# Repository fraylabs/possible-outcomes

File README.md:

# Fray Labs Outcomes

Public, reusable AI Outcomes and the recipes behind them, published by Fray Labs for [Possible](https://possible.sh).

Each folder contains:

- `outcome.md` — what was made and the original request;
- `prompt.md` — the recorded reusable execution prompt; and
- `outcome.json` — provenance, models, Products, Skills, requirements, file metadata, and an optional recipe.

A recipe collects the recorded agent, pinned skills, references, tools and ordered steps that help another agent reproduce or adapt the result. Unknown details are omitted. Fray-authored backfills explicitly label steps reconstructed from published prompts and artifacts; they are not transcripts of historical agent turns. Existing model provenance, prompts, result limitations and creator credits remain intact. Curated third-party demos retain their disclosed prompts without an invented workflow.

The root [`outcomes.json`](./outcomes.json) is the machine-readable publisher index. Possible reads this repository directly; the canonical source remains here.

## Use with Possible

Use CLI 0.5.0 or newer for manifests containing the optional `recipe` field. The older primary Product/Skill parsing issue in CLI 0.3.0 was fixed in 0.3.1; recipe support began in 0.4.0; explicit reconstructed-origin labels require 0.5.0.

```shell
npx https://github.com/fraylabs/possible/releases/download/v0.5.0/fraylabs-possible-0.5.0.tgz add fraylabs/possible-outcomes
npx https://github.com/fraylabs/possible/releases/download/v0.5.0/fraylabs-possible-0.5.0.tgz use fraylabs/possible-outcomes@digital-photo-frame
```

The `use` command provides the reusable instructions for an agent. Review the recipe, original prompt and stated limits before running it; access to referenced tools and services is still required.

## Opus 5.5 demos

[See ten creator demos and copy their prompts](OPUS-DEMOS.md): neon cities, mini golf, a cursor-following pet, a rocket launch, an interactive robot hand, fluid simulation, a Rube Goldberg machine, a sunset pirate ship, motion design and an explorable pagoda. Each links the original creator and records creator-reported model provenance.

## License

Fray-authored code and text are available under the MIT License. Curated creator prompts and demo media retain their original ownership and are excluded from that grant; see linked sources and each media/NOTICE.md. Referenced third-party Products and Skills retain their respective ownership and licenses.

CLI 0.5.0 is currently distributed through the verified GitHub release package used above. The npm registry remains on 0.3.1; use the release package for these optional recipes.

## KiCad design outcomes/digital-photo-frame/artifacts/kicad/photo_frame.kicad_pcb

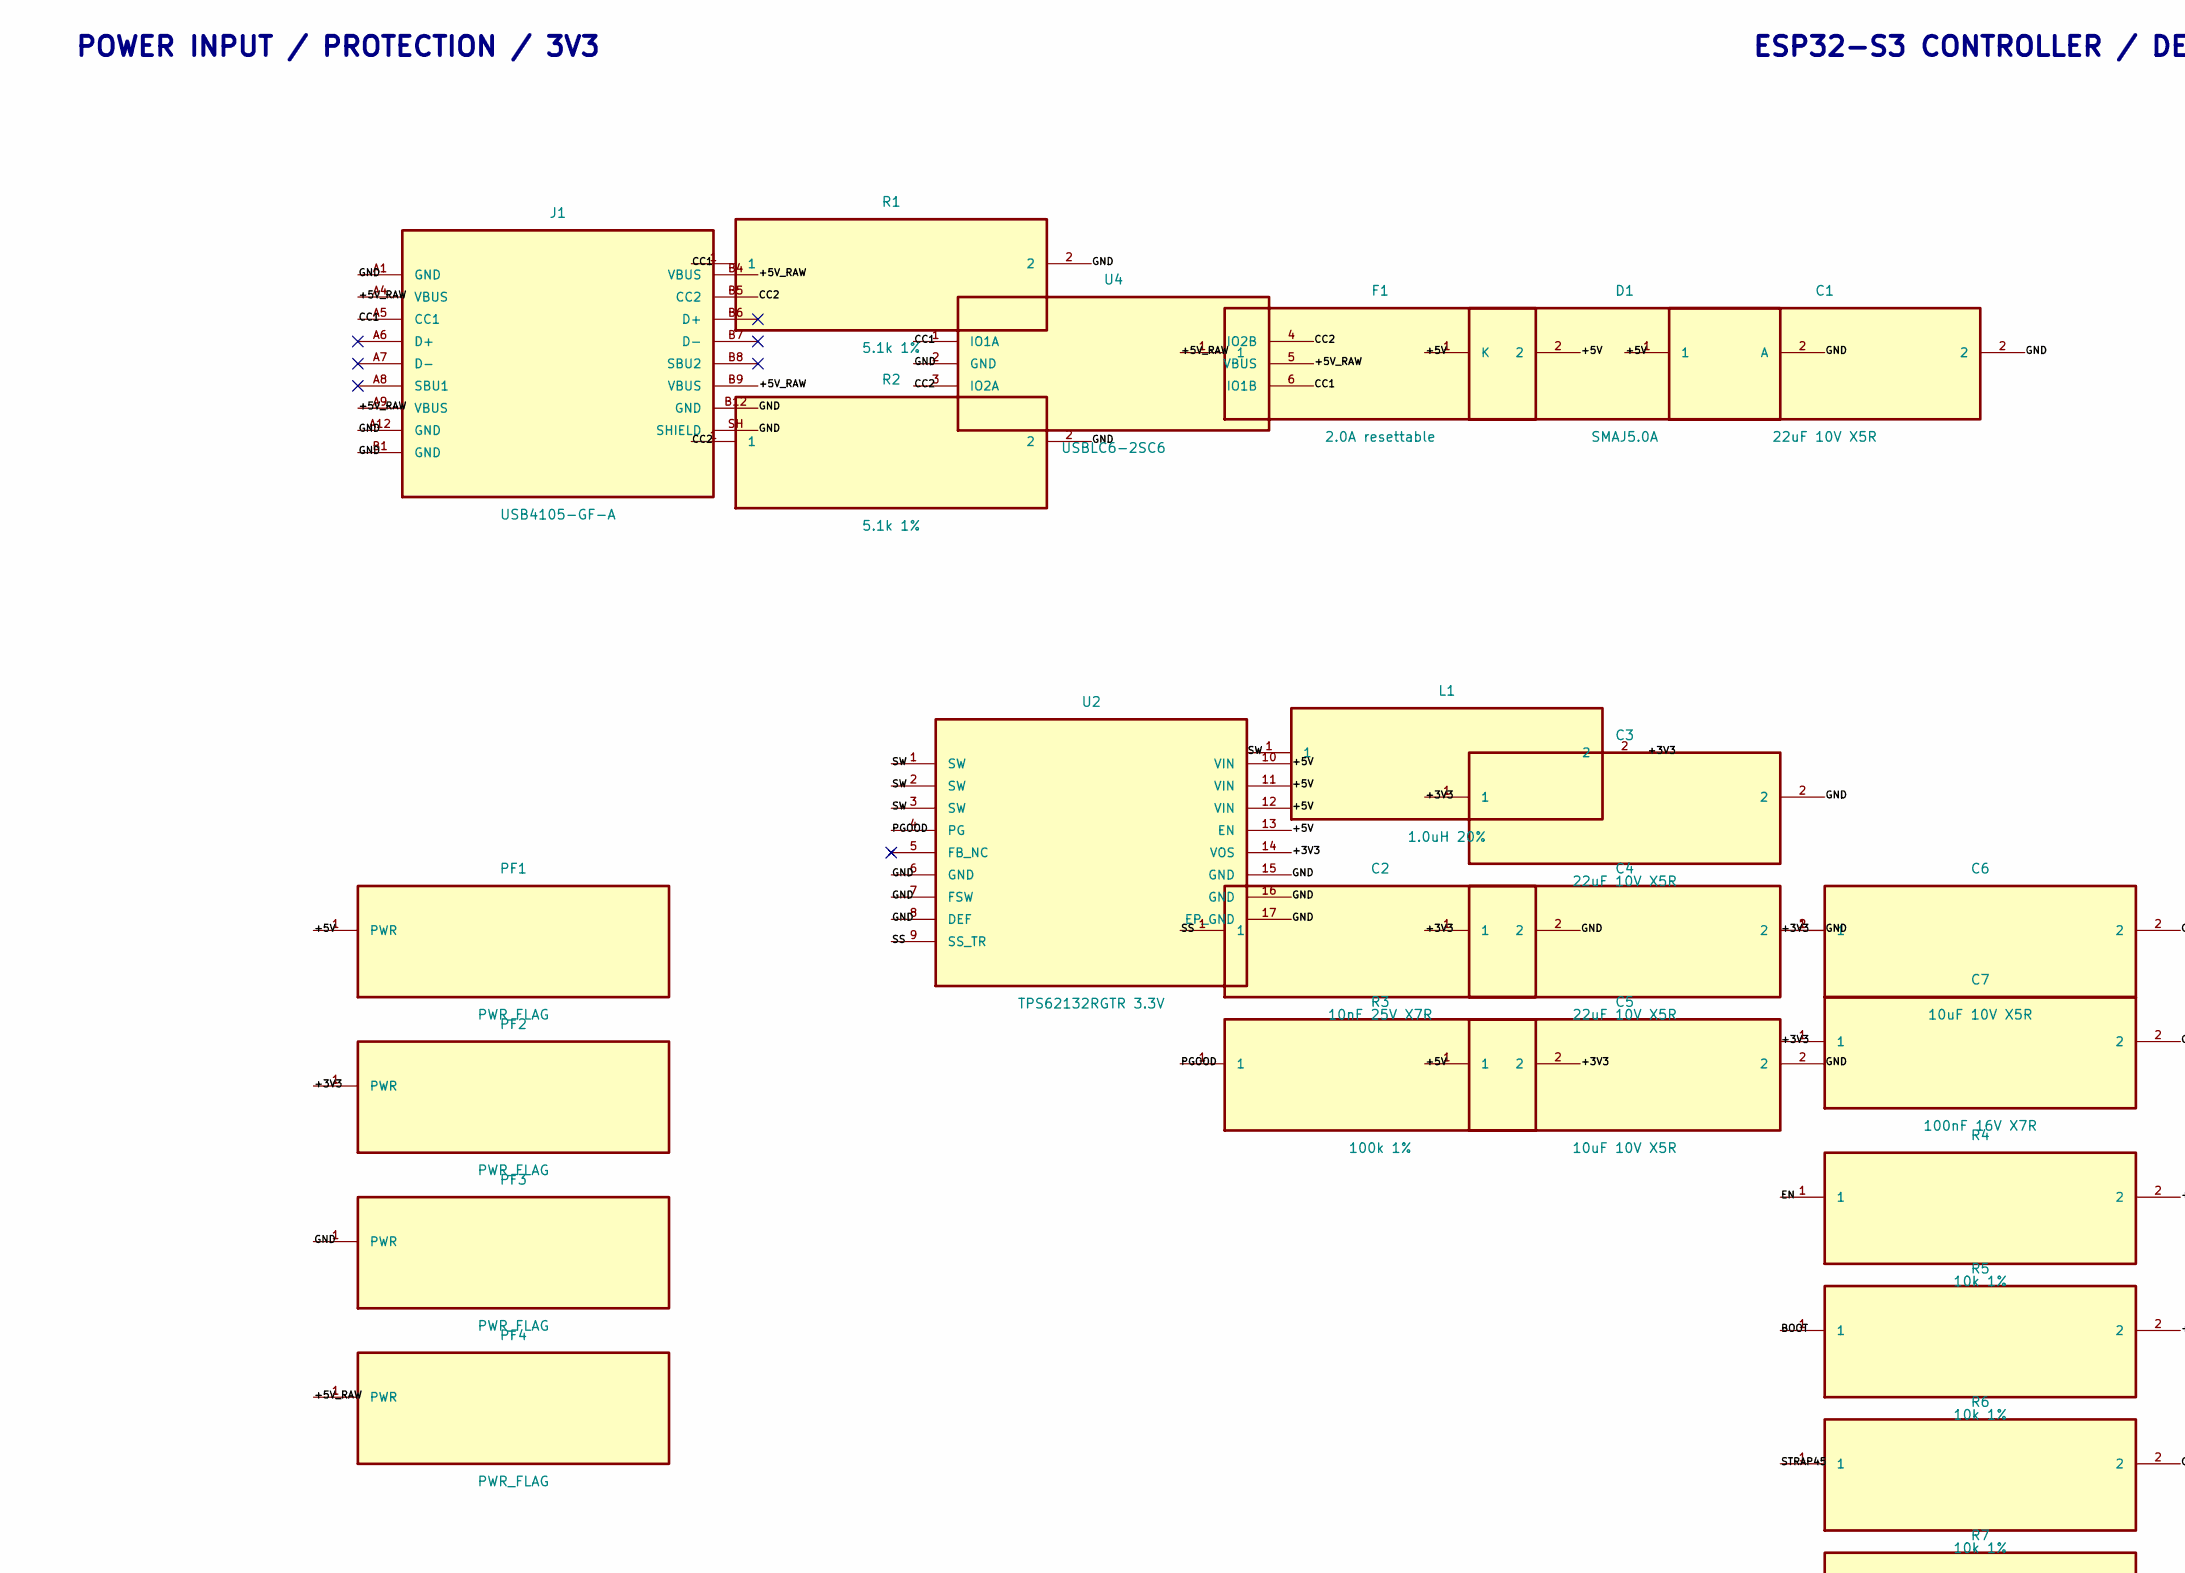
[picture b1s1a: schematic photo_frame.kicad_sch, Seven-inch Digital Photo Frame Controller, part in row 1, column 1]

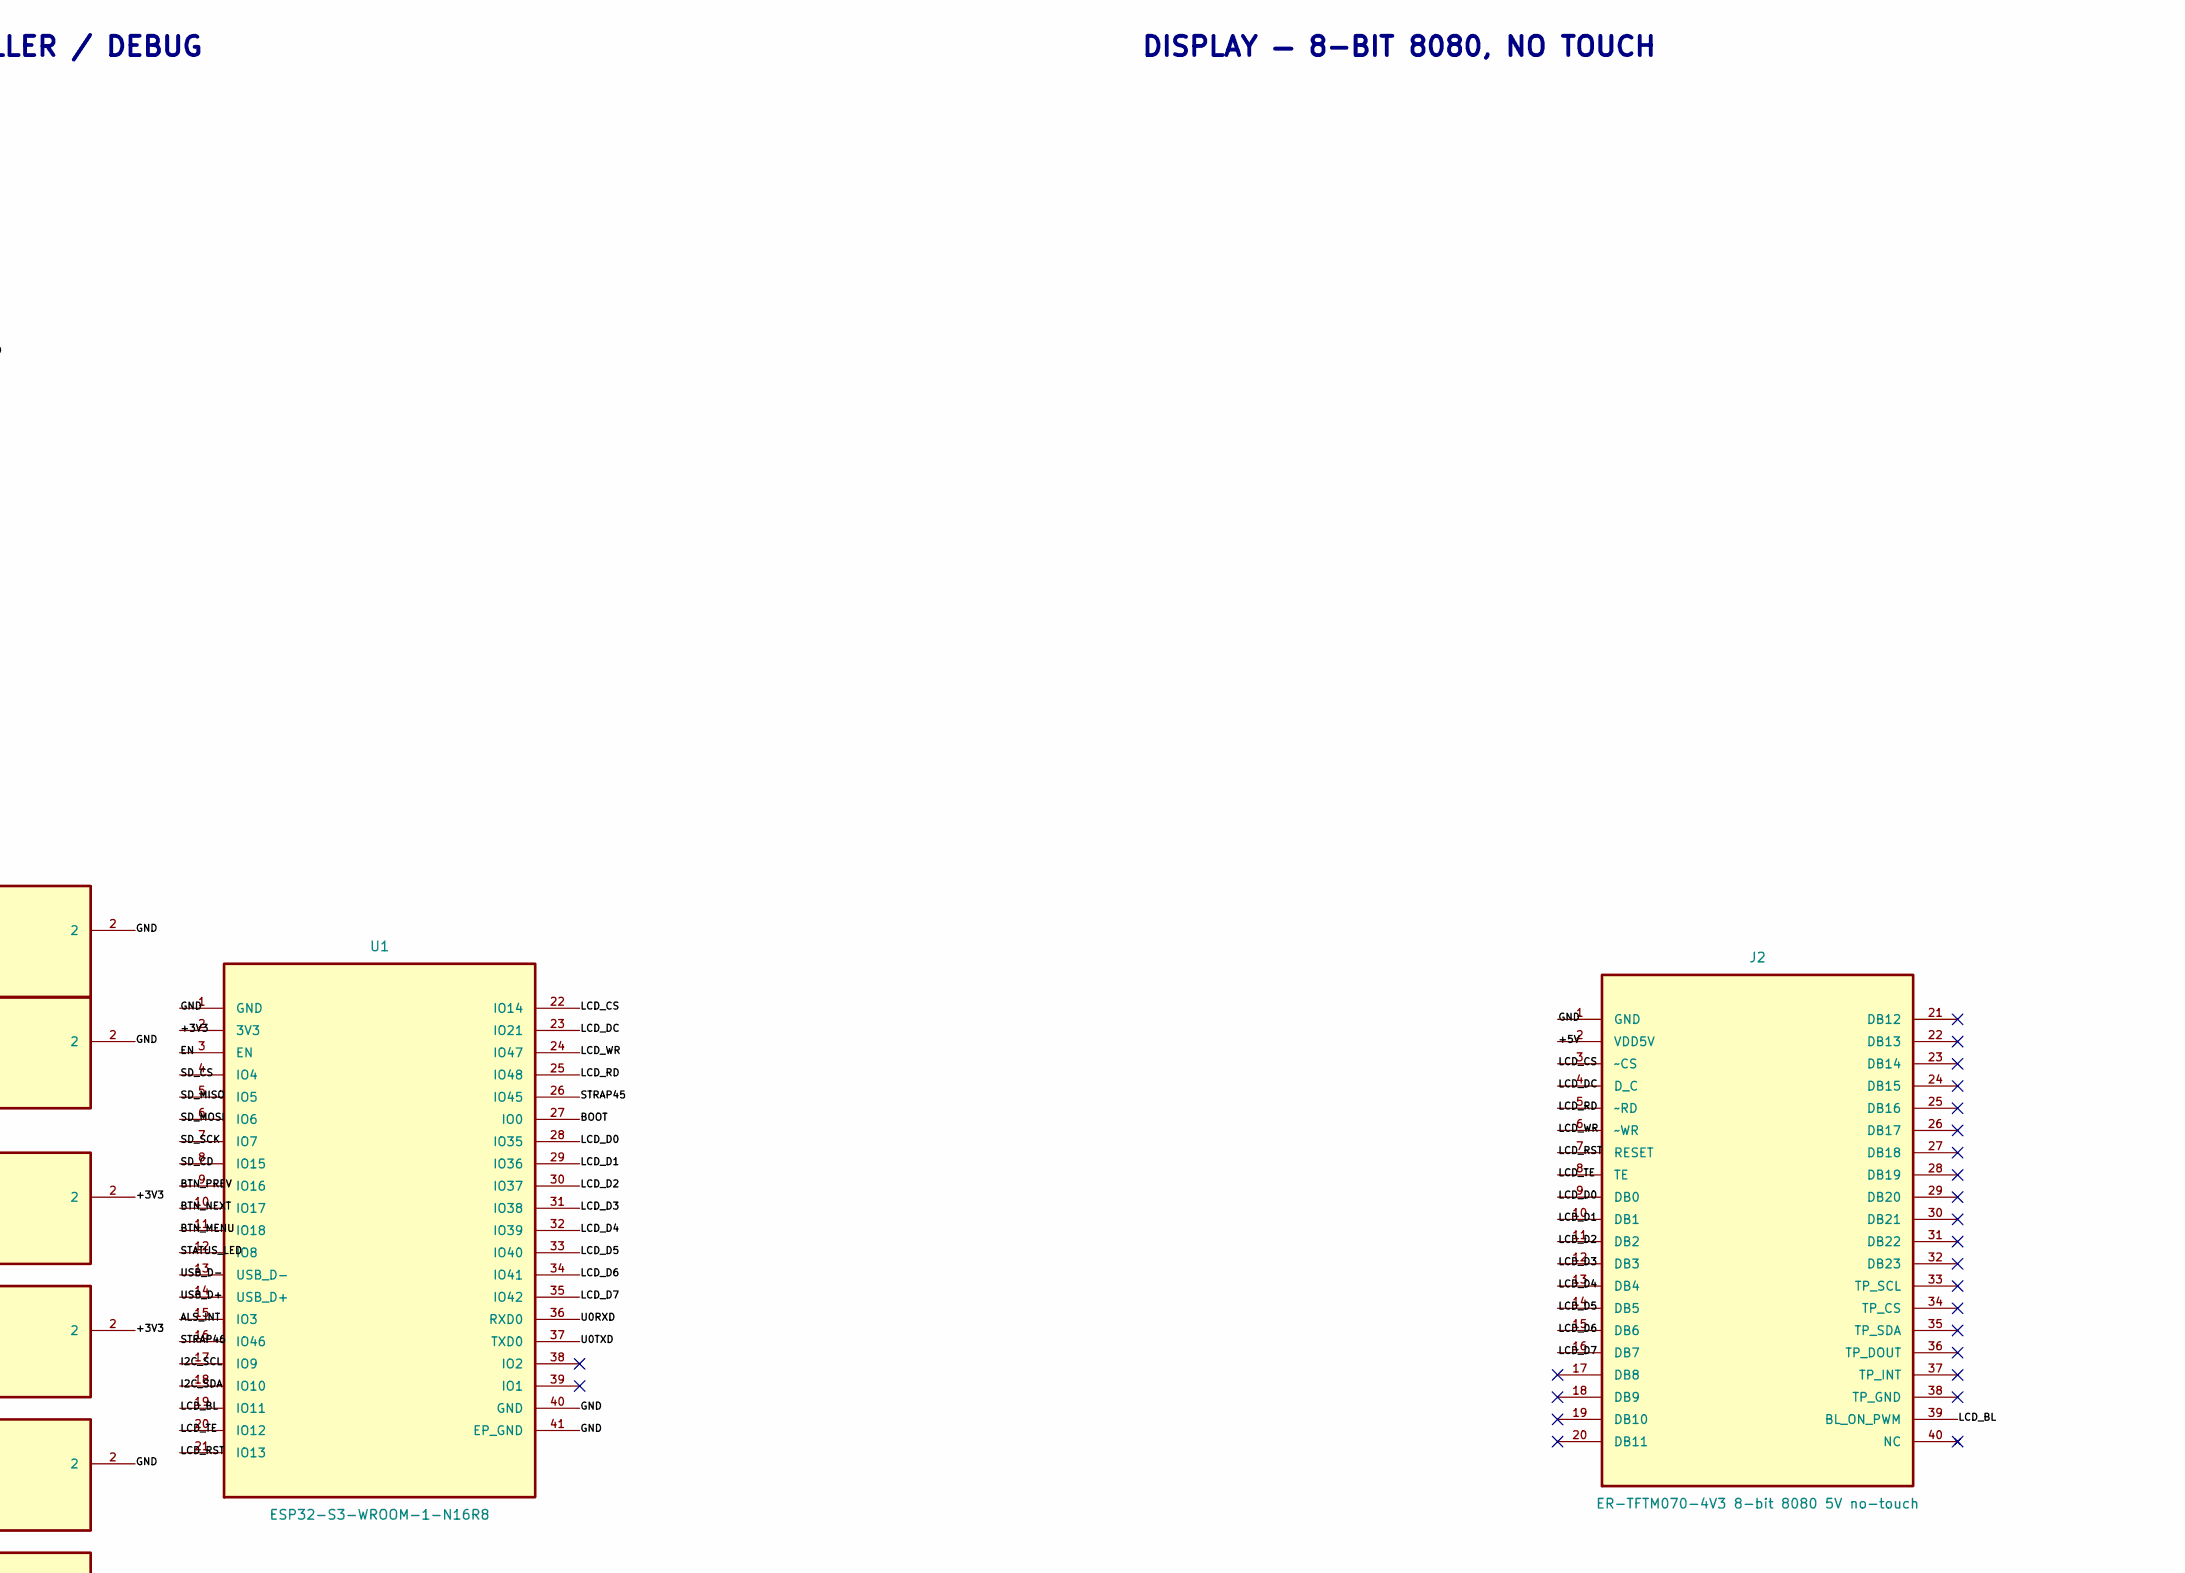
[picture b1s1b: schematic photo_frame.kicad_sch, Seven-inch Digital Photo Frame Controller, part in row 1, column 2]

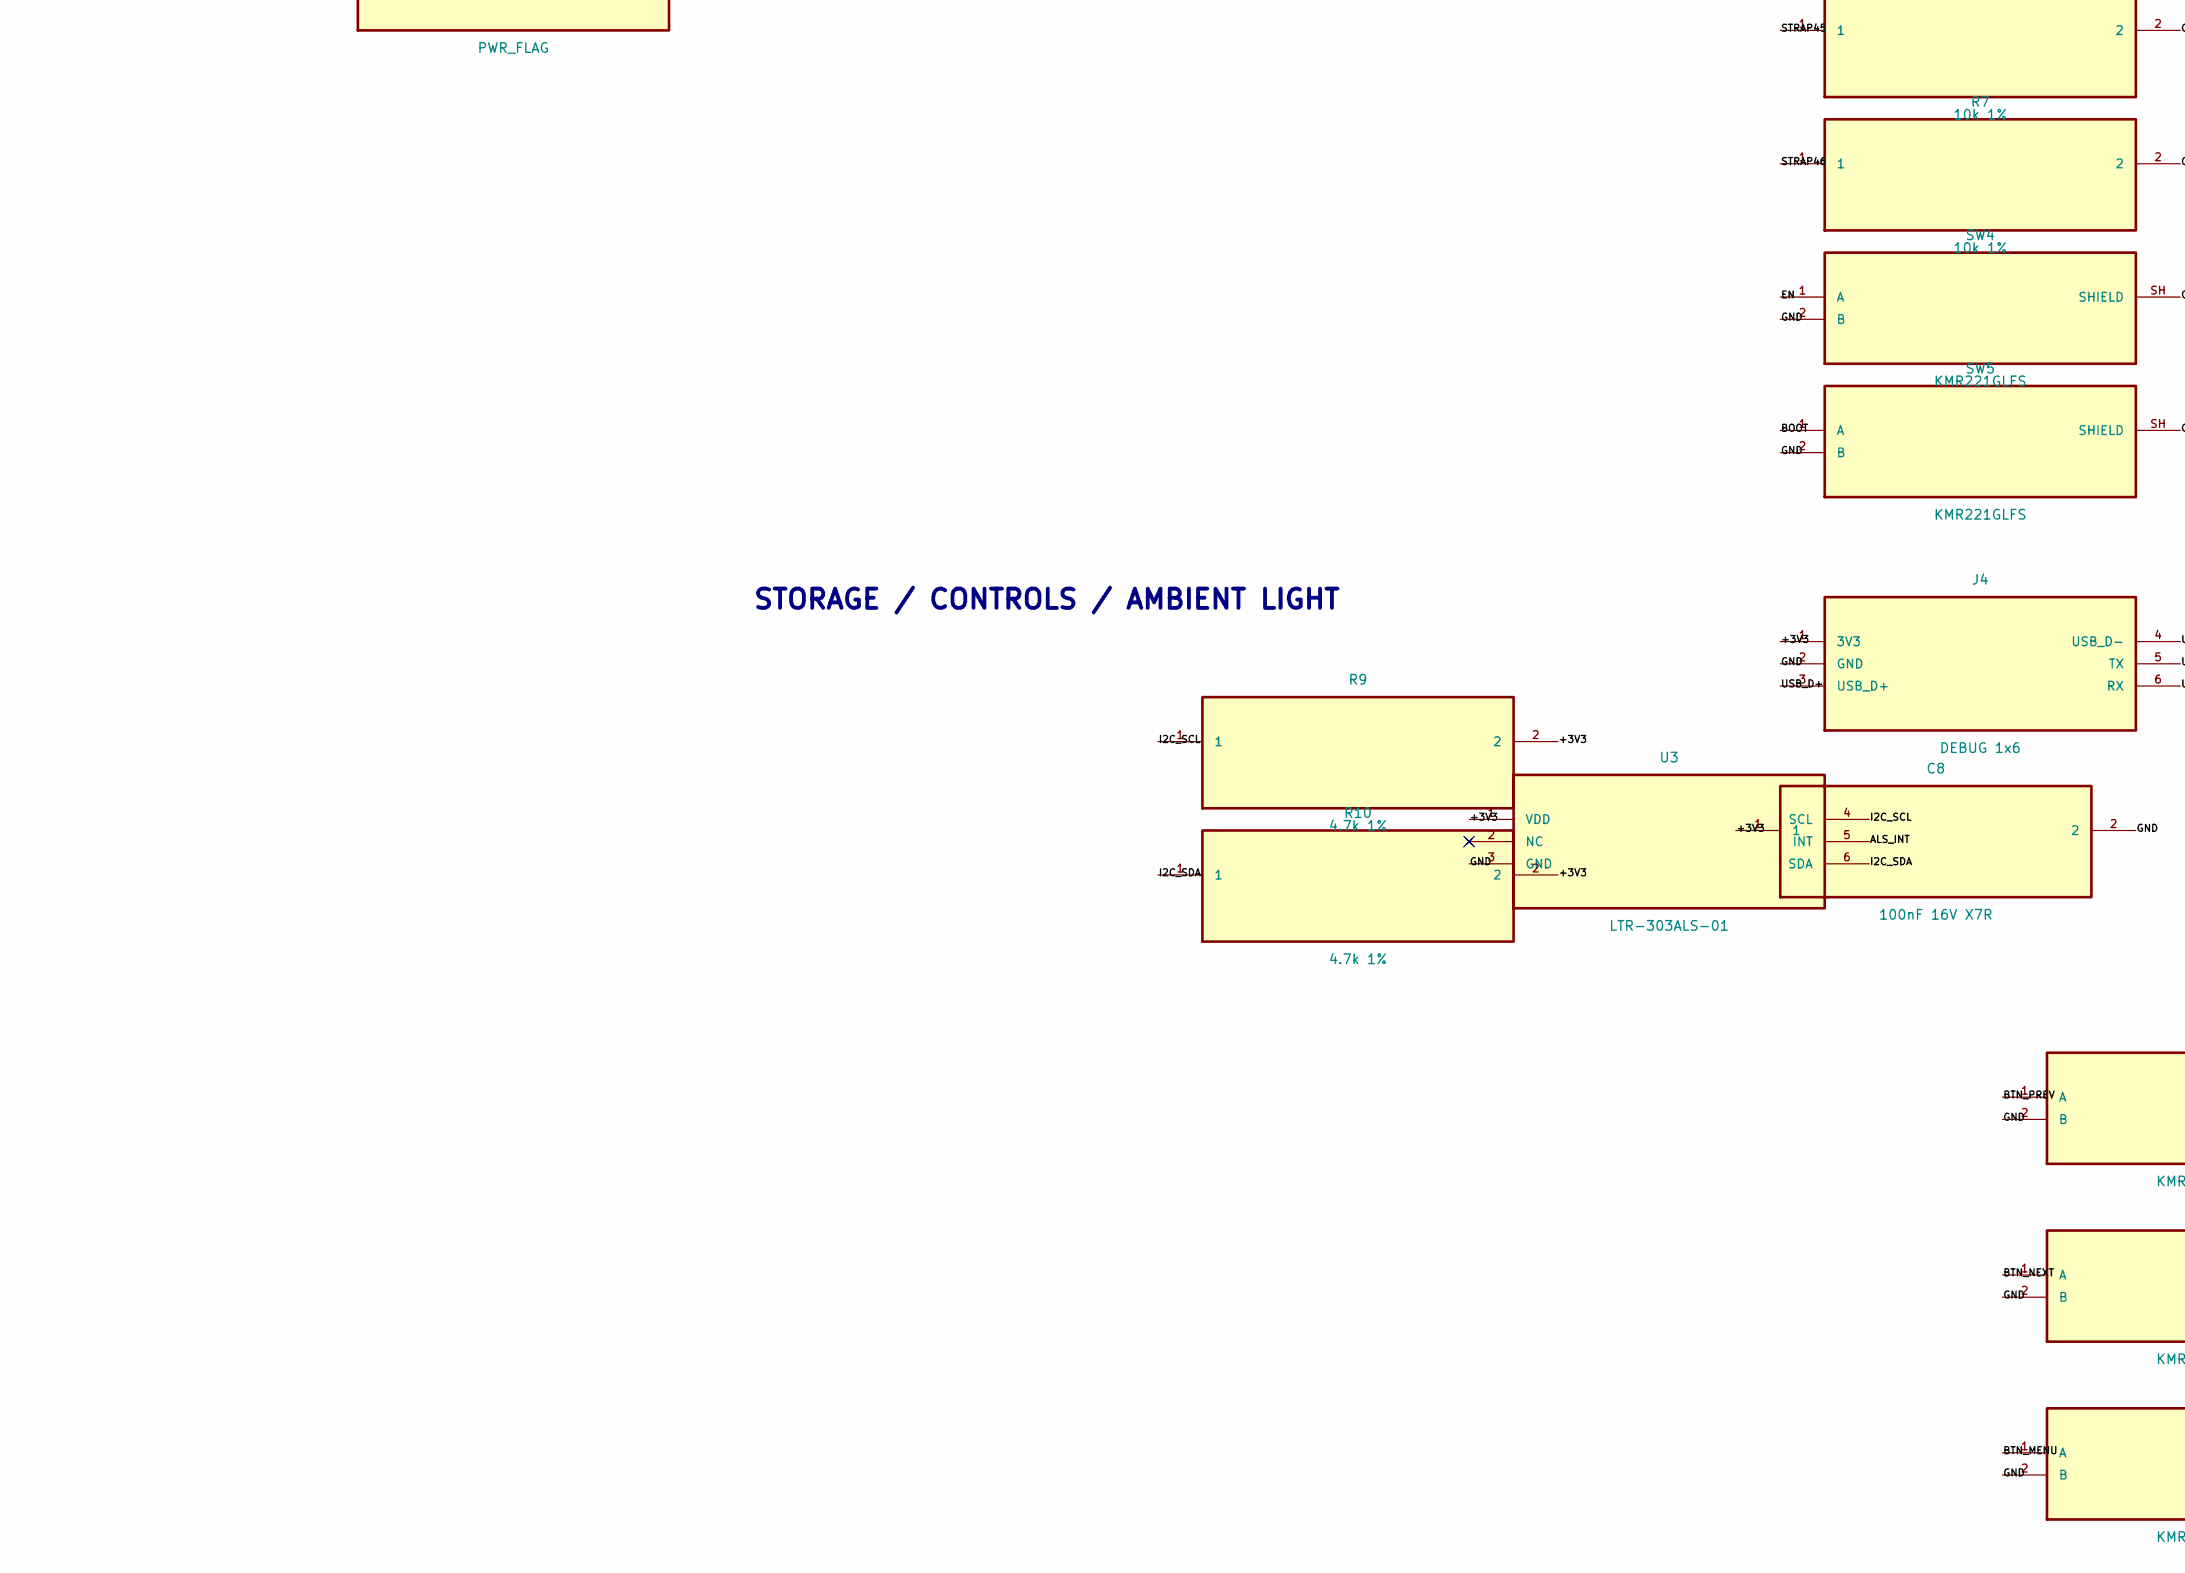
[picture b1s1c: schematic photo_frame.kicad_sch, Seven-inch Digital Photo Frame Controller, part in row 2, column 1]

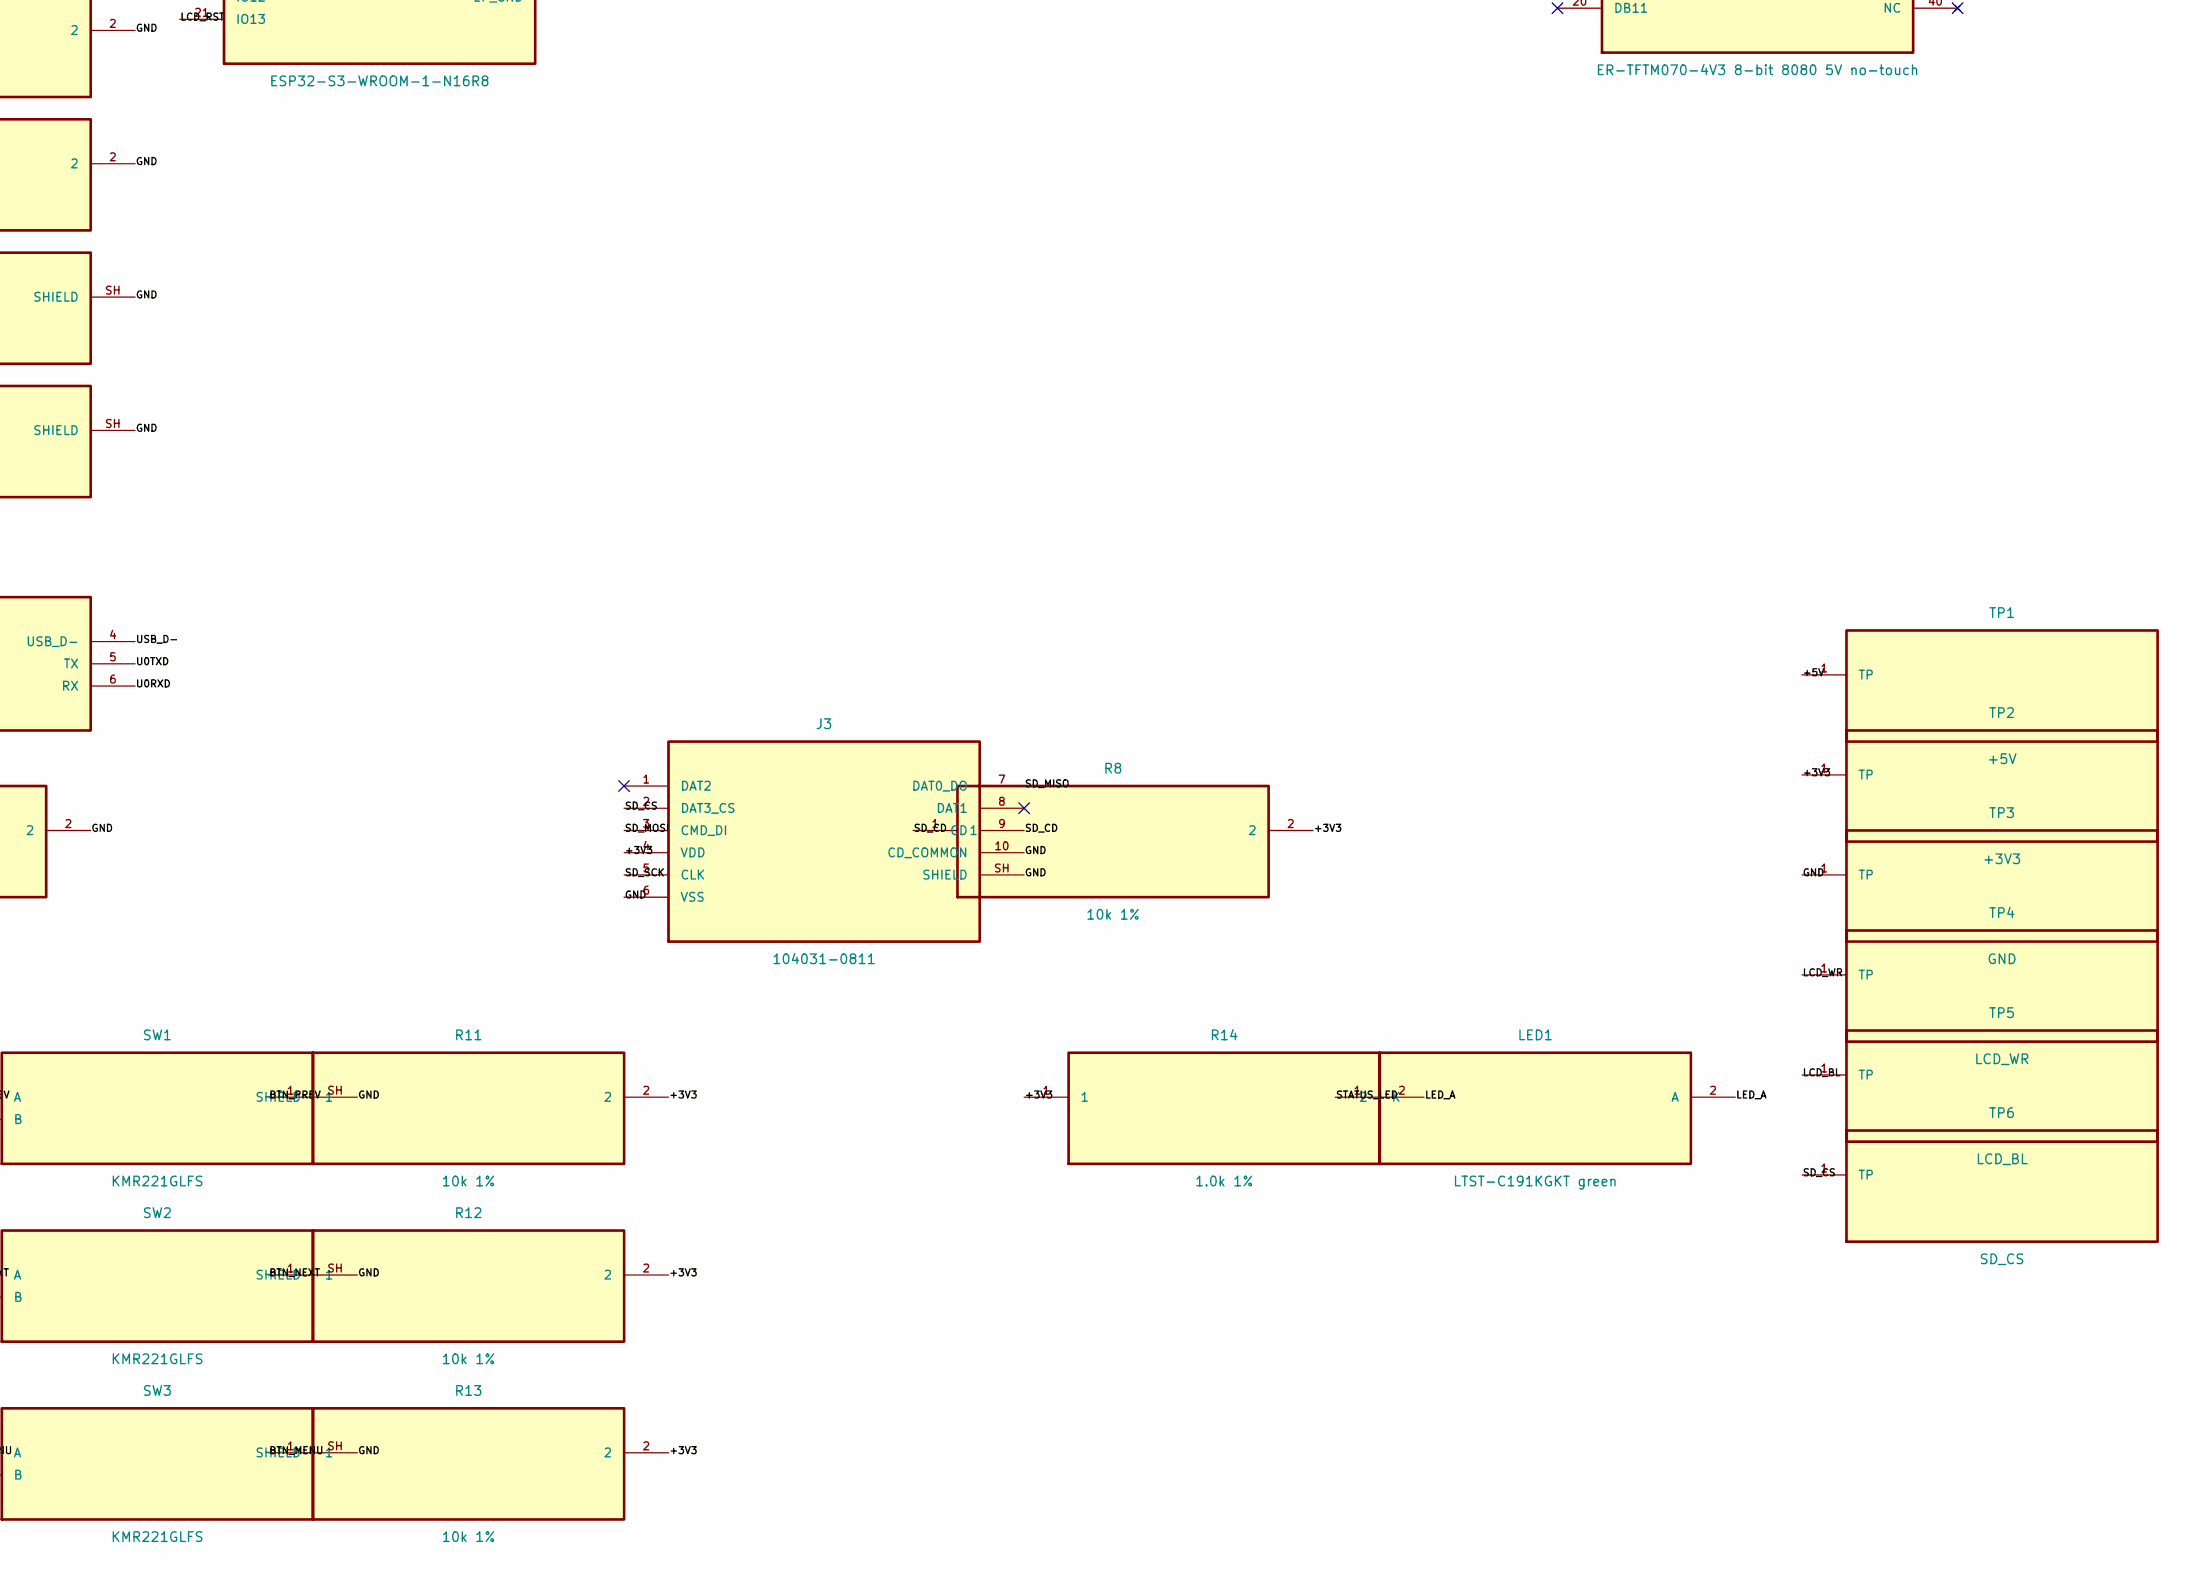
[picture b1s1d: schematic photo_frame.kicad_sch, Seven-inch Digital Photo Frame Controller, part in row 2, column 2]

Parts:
C1, C3, C4: 22uF 10V X5R; C_0805_2012Metric; MPN GRM21BR61A226ME44L
C2: 10nF 25V X7R; C_0603_1608Metric; MPN GRM188R71E103KA01D
C5, C6: 10uF 10V X5R; C_0805_2012Metric; MPN GRM21BR61A106KE19L
C7, C8: 100nF 16V X7R; C_0603_1608Metric; MPN GRM188R71C104KA01D
D1: SMAJ5.0A; D_SMA; MPN SMAJ5.0A
F1: 2.0A resettable; Fuse_1206_3216Metric; MPN MF-MSMF200-2
J1: USB4105-GF-A; USB_C_Receptacle_GCT_USB4105-xx-A_16P_TopMnt_Horizontal; MPN USB4105-GF-A
J2: ER-TFTM070-4V3 8-bit 8080 5V no-touch; PinHeader_2x20_P2.54mm_Vertical; MPN ER-TFTM070-4V3
J3: 104031-0811; microSD_HC_Molex_104031-0811; MPN 104031-0811
J4: DEBUG 1x6; PinHeader_1x06_P2.54mm_Vertical; MPN M20-9990646
L1: 1.0uH 20%; L_Bourns-SRU8028_8.0x8.0mm; MPN XAL4020-102MEC
LED1: LTST-C191KGKT green; LED_0603_1608Metric; MPN LTST-C191KGKT
PF1, PF2, PF3, PF4: PWR_FLAG
R1, R2: 5.1k 1%; R_0603_1608Metric; MPN RC0603FR-075K1L
R3: 100k 1%; R_0603_1608Metric; MPN RC0603FR-07100KL
R4, R5, R6, R7, R8, R11, R12, R13: 10k 1%; R_0603_1608Metric; MPN RC0603FR-0710KL
R9, R10: 4.7k 1%; R_0603_1608Metric; MPN RC0603FR-074K7L
R14: 1.0k 1%; R_0603_1608Metric; MPN RC0603FR-071KL
SW1, SW2, SW3, SW4, SW5: KMR221GLFS; SW_Push_1P1T-SH_NO_CK_KMR2xxG; MPN KMR221GLFS
TP1: +5V; TestPoint_Pad_D1.5mm; MPN 5015
TP2: +3V3; TestPoint_Pad_D1.5mm; MPN 5015
TP3: GND; TestPoint_Pad_D1.5mm; MPN 5015
TP4: LCD_WR; TestPoint_Pad_D1.5mm; MPN 5015
TP5: LCD_BL; TestPoint_Pad_D1.5mm; MPN 5015
TP6: SD_CS; TestPoint_Pad_D1.5mm; MPN 5015
U1: ESP32-S3-WROOM-1-N16R8; ESP32-S3-WROOM-1; MPN ESP32-S3-WROOM-1-N16R8
U2: TPS62132RGTR 3.3V; VQFN-16-1EP_3x3mm_P0.5mm_EP1.68x1.68mm_ThermalVias; MPN TPS62132RGTR
U3: LTR-303ALS-01; Lite-On_LTR-303ALS-01; MPN LTR-303ALS-01
U4: USBLC6-2SC6; SOT-23-6; MPN USBLC6-2SC6

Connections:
+3V3: C3.1, C4.1, C6.1, C7.1, C8.1, J3.4 (VDD), J4.1 (3V3), L1.2, PF2.1, R3.2, R4.2, R5.2, R8.2, R9.2, R10.2, R11.2, R12.2, R13.2, R14.1, TP2.1, U1.2 (3V3), U2.14 (VOS), U3.1 (VDD)
+5V: C1.1, C5.1, D1.1 (K), F1.2, J2.2 (VDD5V), PF1.1, TP1.1, U2.10 (VIN), U2.11 (VIN), U2.12 (VIN), U2.13 (EN)
+5V_RAW: F1.1, J1.A4 (VBUS), J1.A9 (VBUS), J1.B4 (VBUS), J1.B9 (VBUS), PF4.1, U4.5 (VBUS)
ALS_INT: U1.15 (IO3), U3.5 (INT)
BOOT: R5.1, SW5.1 (A), U1.27 (IO0)
BTN_MENU: R13.1, SW3.1 (A), U1.11 (IO18)
BTN_NEXT: R12.1, SW2.1 (A), U1.10 (IO17)
BTN_PREV: R11.1, SW1.1 (A), U1.9 (IO16)
CC1: J1.A5 (CC1), R1.1, U4.1 (IO1A), U4.6 (IO1B)
CC2: J1.B5 (CC2), R2.1, U4.3 (IO2A), U4.4 (IO2B)
EN: R4.1, SW4.1 (A), U1.3 (EN)
GND: C1.2, C2.2, C3.2, C4.2, C5.2, C6.2, C7.2, C8.2, D1.2 (A), J1.A1 (GND), J1.A12 (GND), J1.B1 (GND), J1.B12 (GND), J1.SH (SHIELD), J2.1 (GND), J3.6 (VSS), J3.10 (CD_COMMON), J3.SH (SHIELD), J4.2 (GND), PF3.1, R1.2, R2.2, R6.2, R7.2, SW1.2 (B), SW1.SH (SHIELD), SW2.2 (B), SW2.SH (SHIELD), SW3.2 (B), SW3.SH (SHIELD), SW4.2 (B), SW4.SH (SHIELD), SW5.2 (B), SW5.SH (SHIELD), TP3.1, U1.1 (GND), U1.40 (GND), U1.41 (EP_GND), U2.6 (GND), U2.7 (FSW), U2.8 (DEF), U2.15 (GND), U2.16 (GND), U2.17 (EP_GND), U3.3 (GND), U4.2 (GND)
I2C_SCL: R9.1, U1.17 (IO9), U3.4 (SCL)
I2C_SDA: R10.1, U1.18 (IO10), U3.6 (SDA)
LCD_BL: J2.39 (BL_ON_PWM), TP5.1, U1.19 (IO11)
LCD_CS: J2.3 (~CS), U1.22 (IO14)
LCD_D0: J2.9 (DB0), U1.28 (IO35)
LCD_D1: J2.10 (DB1), U1.29 (IO36)
LCD_D2: J2.11 (DB2), U1.30 (IO37)
LCD_D3: J2.12 (DB3), U1.31 (IO38)
LCD_D4: J2.13 (DB4), U1.32 (IO39)
LCD_D5: J2.14 (DB5), U1.33 (IO40)
LCD_D6: J2.15 (DB6), U1.34 (IO41)
LCD_D7: J2.16 (DB7), U1.35 (IO42)
LCD_DC: J2.4 (D_C), U1.23 (IO21)
LCD_RD: J2.5 (~RD), U1.25 (IO48)
LCD_RST: J2.7 (RESET), U1.21 (IO13)
LCD_TE: J2.8 (TE), U1.20 (IO12)
LCD_WR: J2.6 (~WR), TP4.1, U1.24 (IO47)
LED_A: LED1.2 (A), R14.2
PGOOD: R3.1, U2.4 (PG)
SD_CD: J3.9 (CD), R8.1, U1.8 (IO15)
SD_CS: J3.2 (DAT3_CS), TP6.1, U1.4 (IO4)
SD_MISO: J3.7 (DAT0_DO), U1.5 (IO5)
SD_MOSI: J3.3 (CMD_DI), U1.6 (IO6)
SD_SCK: J3.5 (CLK), U1.7 (IO7)
SS: C2.1, U2.9 (SS_TR)
STATUS_LED: LED1.1 (K), U1.12 (IO8)
STRAP45: R6.1, U1.26 (IO45)
STRAP46: R7.1, U1.16 (IO46)
SW: L1.1, U2.1 (SW), U2.2 (SW), U2.3 (SW)
U0RXD: J4.6 (RX), U1.36 (RXD0)
U0TXD: J4.5 (TX), U1.37 (TXD0)
USB_D+: J4.3 (USB_D+), U1.14 (USB_D+)
USB_D-: J4.4 (USB_D-), U1.13 (USB_D-)

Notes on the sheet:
DISPLAY — 8-BIT 8080, NO TOUCH
STORAGE / CONTROLS / AMBIENT LIGHT
ESP32-S3 CONTROLLER / DEBUG
POWER INPUT / PROTECTION / 3V3

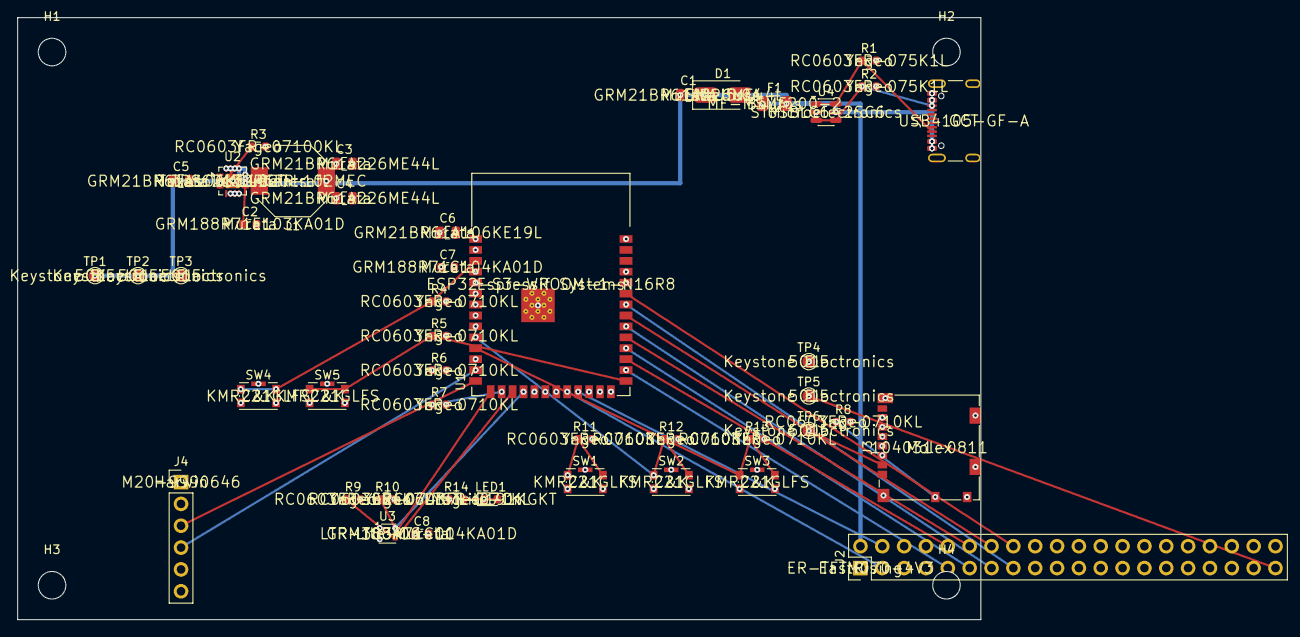
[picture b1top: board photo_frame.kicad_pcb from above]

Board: 4 copper layers, 112.0 x 70.0 mm, 49 parts (0 on the bottom side), 45 nets.

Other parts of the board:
H1, H2, H3, H4: M3 mounting hole; MountingHole_3.2mm_M3
